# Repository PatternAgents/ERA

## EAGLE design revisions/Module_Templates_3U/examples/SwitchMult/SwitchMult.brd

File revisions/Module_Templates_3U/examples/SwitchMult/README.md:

# SwitchMult

Format : ERA / Eurorack

Height : 3U 

Width: 4HP

Depth : 1.0 cm

Power : +12V 35mA

Jacks : 3.5mm Jacks (Thonkiconn PJ301M-12)

A simple, passive, "Switched Multiple" design for ERA/Eurorack. 
Four(4) latching, LED illuminated, pushbutton switches, 
control up to four (4) input/outputs,
that are routed to an internal bus.
The four inputs (P1-P4) are "normalized" to the ERA bus signals as follows:

1) ERA Bus Gate In  (Green)
2) ERA Bus CV In    (Red)
3) ERA Bus Gate Out (Blue)
4) ERA Bus CV Out   (Yellow)

When connected to an ERA backplane, those Bus signals can be routed to other
"Switched Multiple" modules, or other ERA audio/video modules.

-----------------------------------------------------
This repository contains Open Source Hardware Reference Designs for Embedded Rack Architecture (ERA)
that anyone can use or fabricate for themselves.

For more information, please see the [ERA Wiki](https://github.com/halcyonmodular/ERA/wiki)!

Embedded Rack Architecture (ERA) is a new, Open Source Hardware (OSHW) specification for 
Modular Audio/Video equipment that is being co-developed by a number of
cooperating companies and individuals in the audio field,
and is completely backward compatible with Eurorack (Legacy). 

-----------------------------------------------------

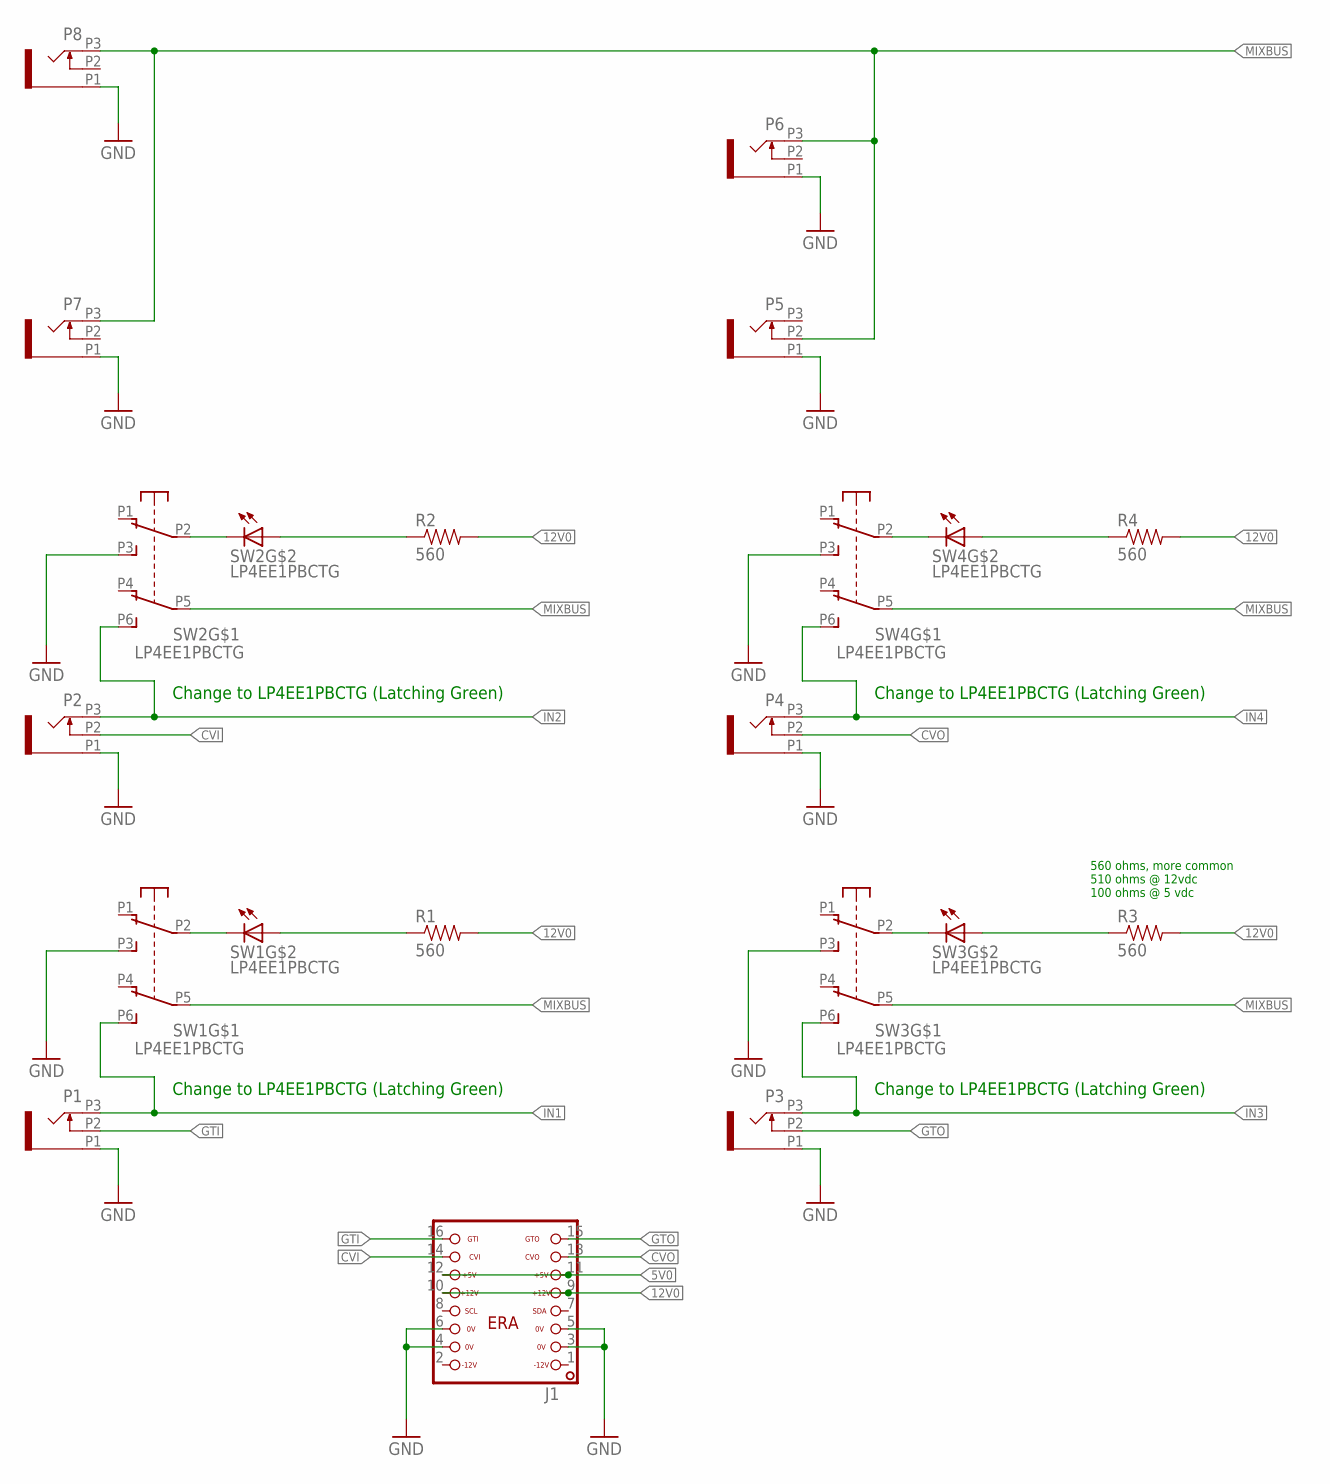
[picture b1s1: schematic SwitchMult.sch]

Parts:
J1: ERA-SHROUD; ERA
P1, P2, P3, P4, P5, P6, P7, P8: PJ301_THONKICONN6; WQP_PJ_301M6
R1, R2, R3, R4: 560; AXIAL-0.4
SW1, SW2, SW3, SW4: LP4EE1PBCTG; LP4OA1PBCT

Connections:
5V0: J1.11, J1.12
12V0: J1.9, J1.10, R1.P$2 (2), R2.P$2 (2), R3.P$2 (2), R4.P$2 (2)
CVI: J1.14, P2.P2 (2)
CVO: J1.13, P4.P2 (2)
GND: J1.3, J1.4, J1.5, J1.6, P1.P1 (1), P2.P1 (1), P3.P1 (1), P4.P1 (1), P5.P1 (1), P6.P1 (1), P7.P1 (1), P8.P1 (1), SW1.P3 (A3), SW2.P3 (A3), SW3.P3 (A3), SW4.P3 (A3)
GTI: J1.16, P1.P2 (2)
GTO: J1.15, P3.P2 (2)
IN1: P1.P3 (3), SW1.P6 (B3)
IN2: P2.P3 (3), SW2.P6 (B3)
IN3: P3.P3 (3), SW3.P6 (B3)
IN4: P4.P3 (3), SW4.P6 (B3)
MIXBUS: P5.P2 (2), P6.P3 (3), P7.P3 (3), P8.P3 (3), SW1.P5 (B2), SW2.P5 (B2), SW3.P5 (B2), SW4.P5 (B2)
unnamed: SW1.L2, SW1.P2 (A2)
unnamed: SW2.L2, SW2.P2 (A2)
unnamed: R1.P$1 (1), SW1.L1
unnamed: R2.P$1 (1), SW2.L1
unnamed: SW3.L2, SW3.P2 (A2)
unnamed: R3.P$1 (1), SW3.L1
unnamed: SW4.L2, SW4.P2 (A2)
unnamed: R4.P$1 (1), SW4.L1

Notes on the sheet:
Change to LP4EE1PBCTG (Latching Green)
560 ohms, more common 510 ohms @ 12vdc 100 ohms @ 5 vdc

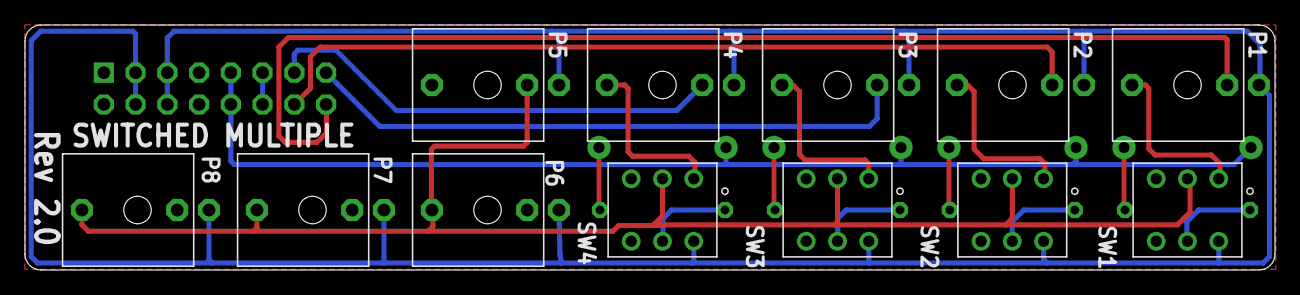
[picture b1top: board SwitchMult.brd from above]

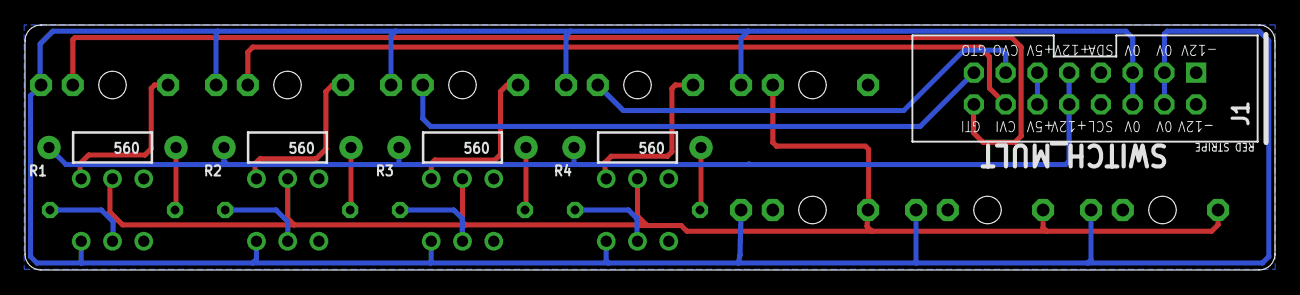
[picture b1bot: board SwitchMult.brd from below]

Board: 2 copper layers, 100.0 x 19.6 mm, 17 parts (5 on the bottom side), 20 nets.

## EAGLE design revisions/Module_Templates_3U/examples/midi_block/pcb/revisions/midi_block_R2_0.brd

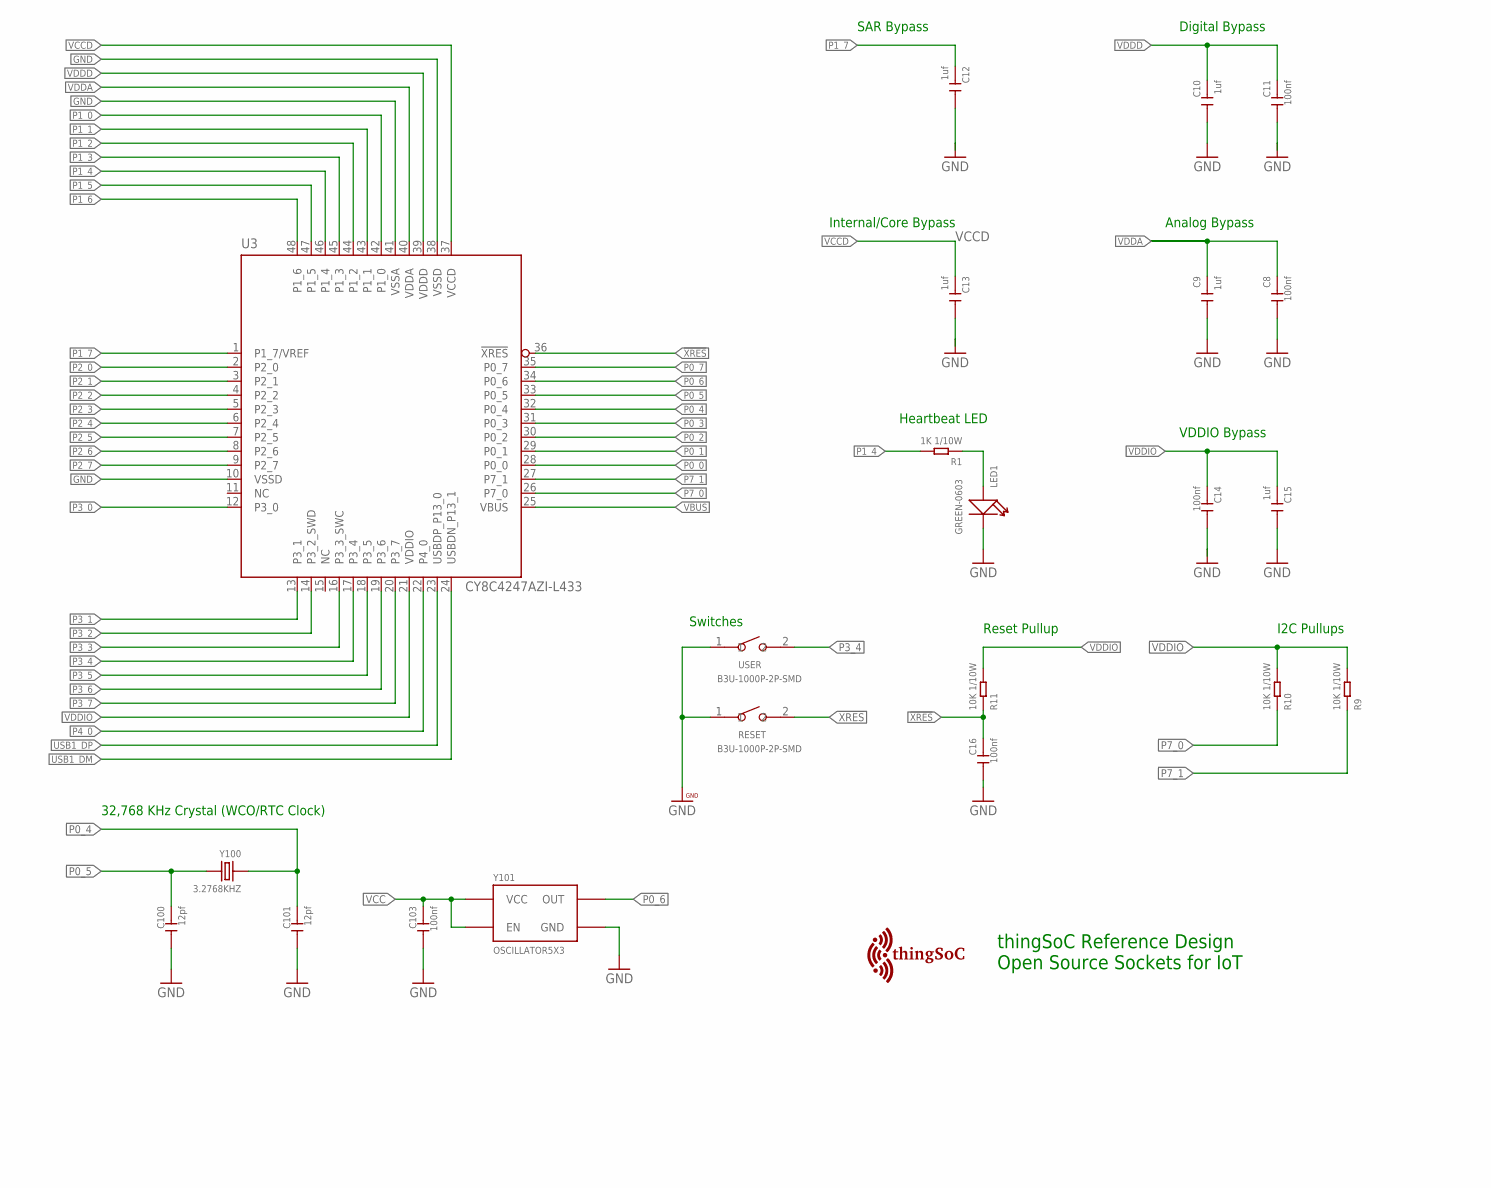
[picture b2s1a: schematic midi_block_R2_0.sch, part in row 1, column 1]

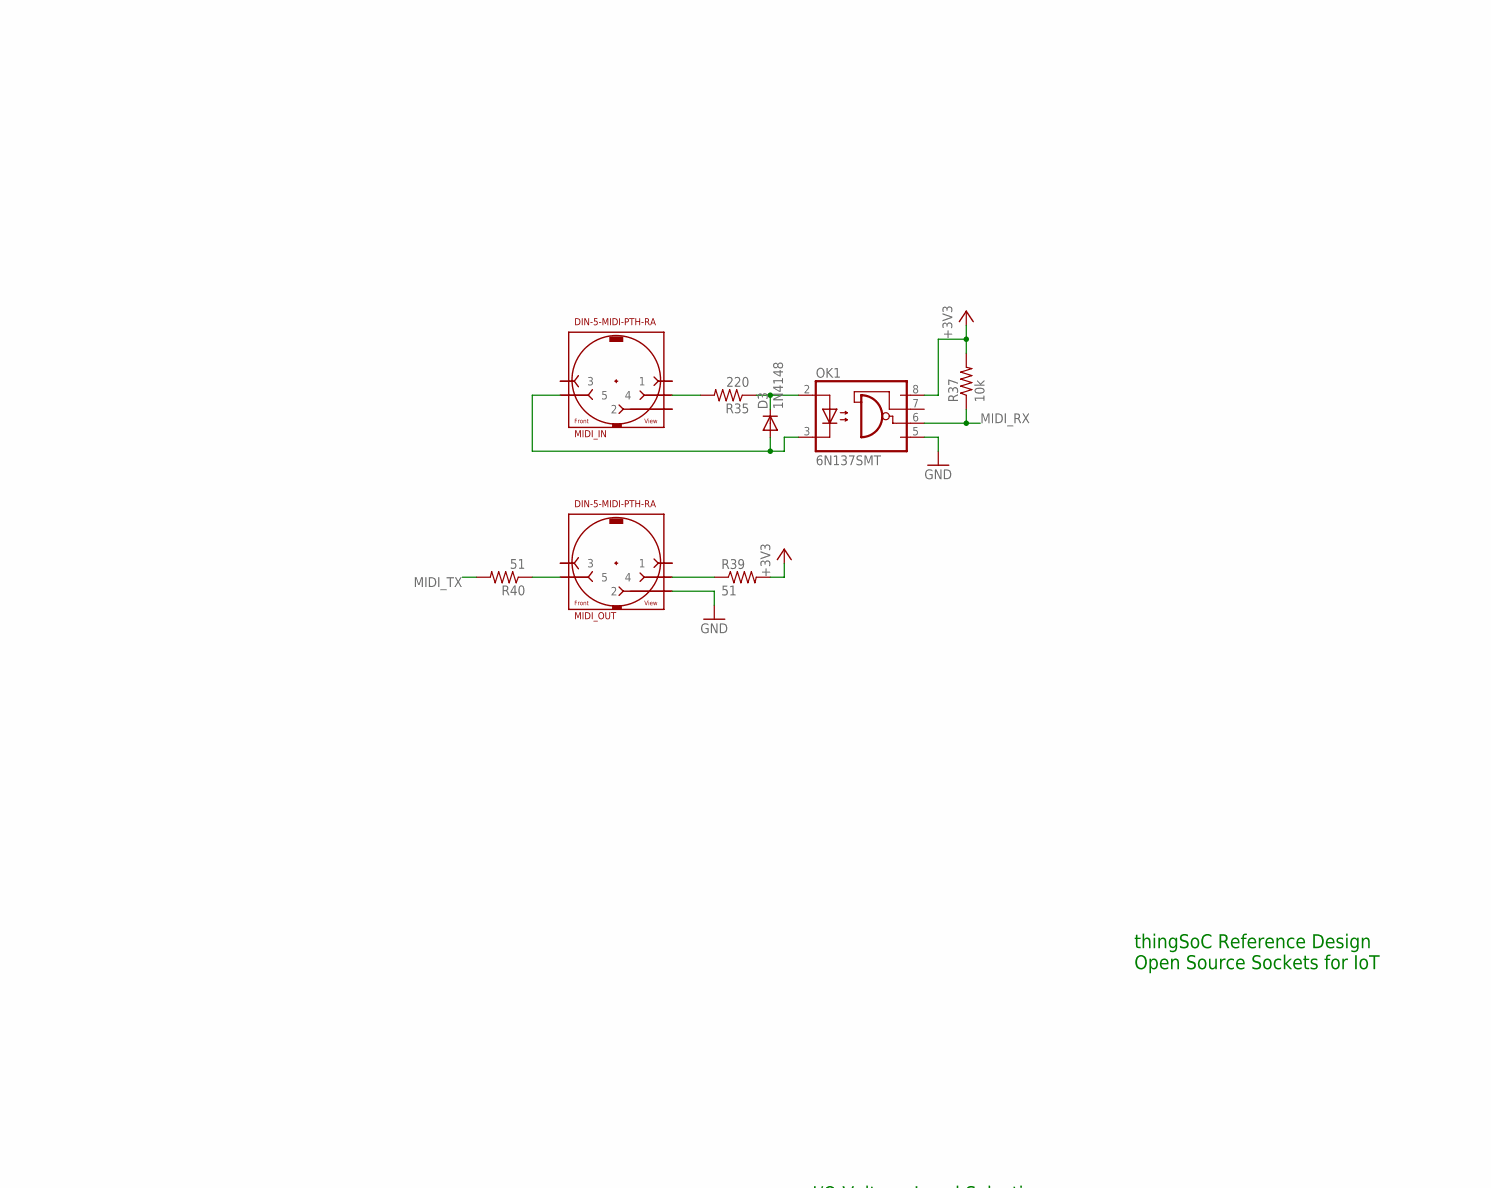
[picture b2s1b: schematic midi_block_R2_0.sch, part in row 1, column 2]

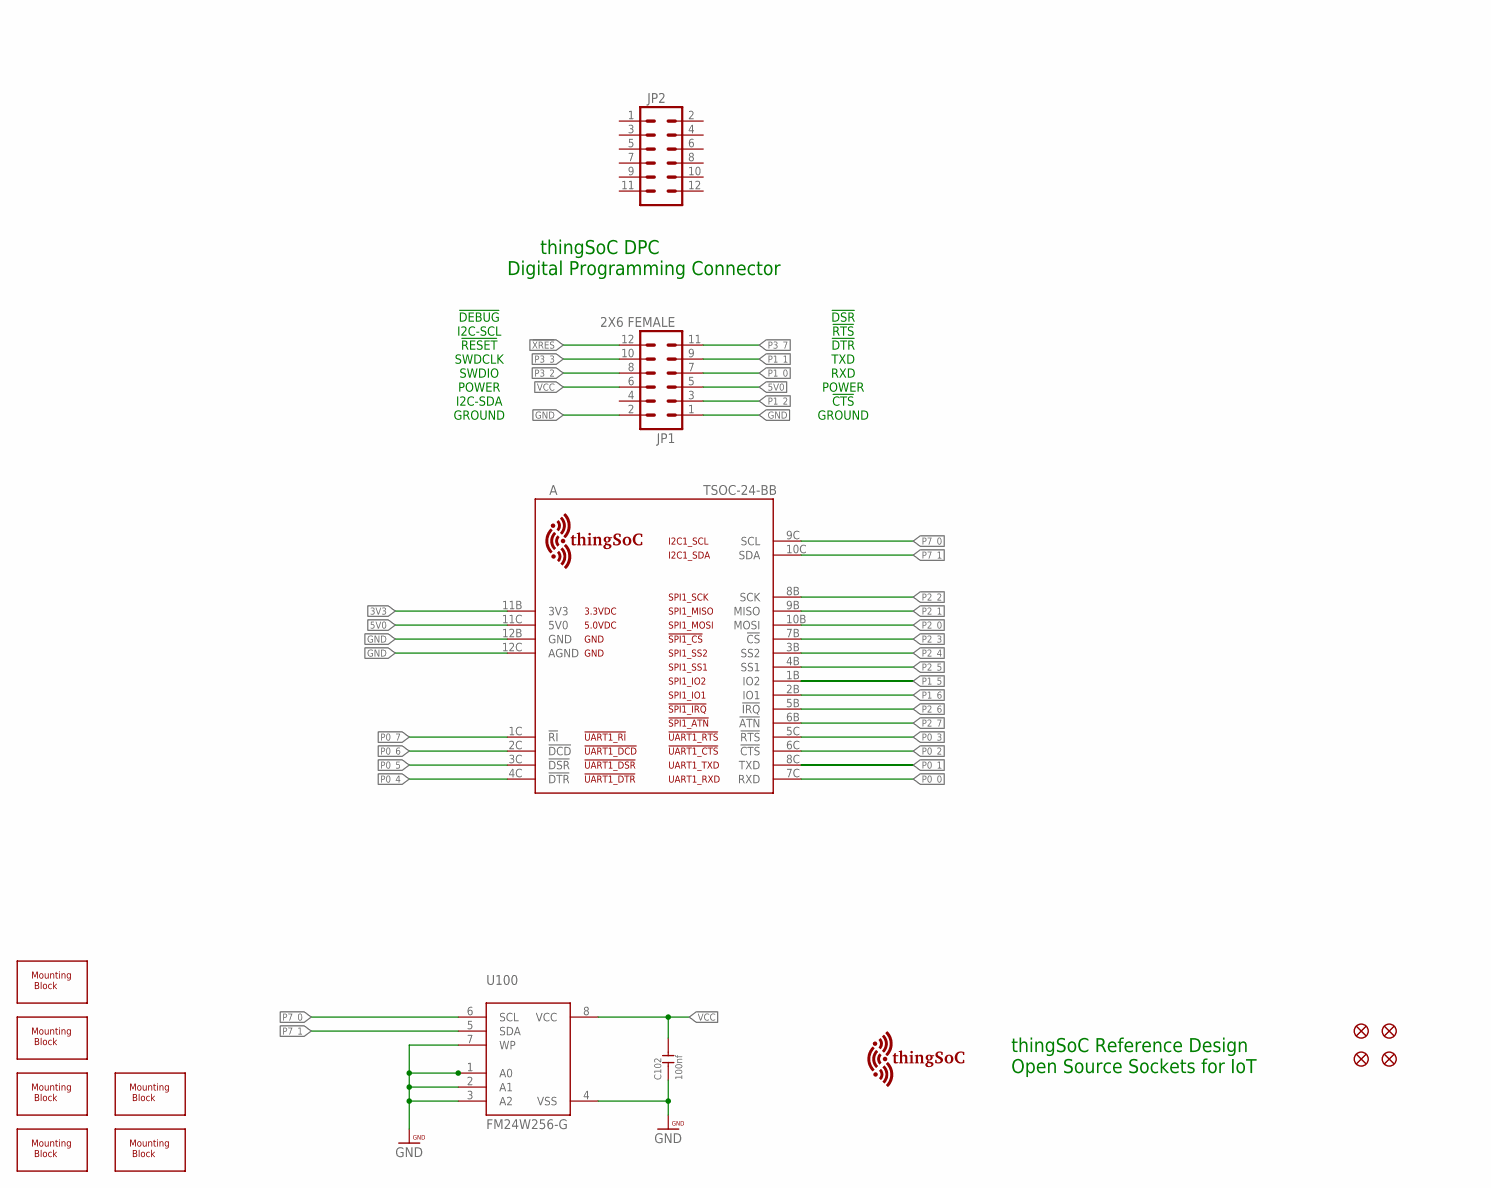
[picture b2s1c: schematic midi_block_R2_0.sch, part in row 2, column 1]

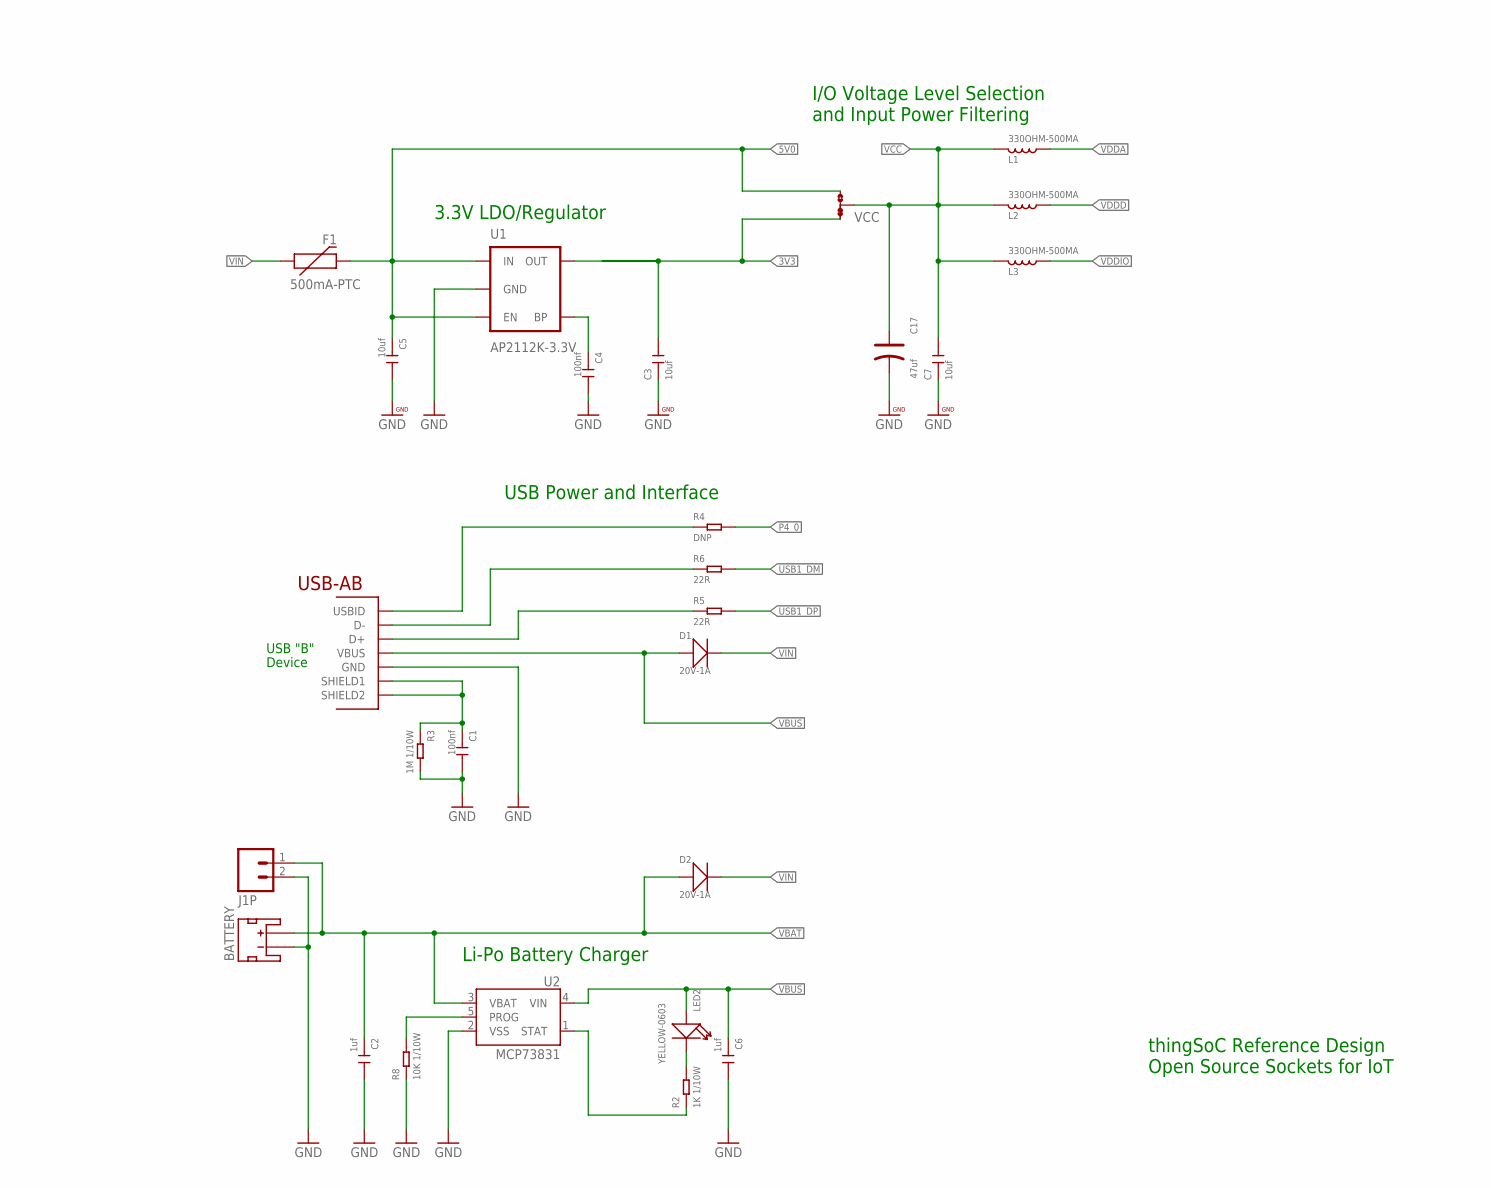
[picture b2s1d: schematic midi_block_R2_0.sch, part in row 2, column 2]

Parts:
A: TSOC-24-BB; TSOC-BB-S24
BATTERY: JST_2MM_MALE; JST-2-SMD
C1, C4, C8, C11, C14, C16, C102, C103: 100nf; C0603
C2, C6, C9, C10, C12, C13, C15: 1uf; C0603
C3, C5, C7: 10uf; C0603
C17: 47uf; AVX-A
C100, C101: 12pf; C0603
D1, D2: 20V-1A; SOD-123
D3: 1N4148; SOD323-W
F1: 500mA-PTC; PTC-1206
FID1, FID2, FID3, FID4: FIDUCIALUFIDUCIAL; MICRO-FIDUCIAL
J1P: M02-JST-2-PTH-NO_SILK; JST-2-PTH-NS
JP1: 2X6 FEMALE; 2X6
JP2: M06X2FEMALE-SMT; 2X6_SMD
L1, L2, L3: 330OHM-500MA; L0603
LED1: GREEN-0603; LED-0603
LED2: YELLOW-0603; LED-0603
MIDI_IN: DIN-5-MIDI-PTH-RA; DIN-5-PTH-RA-SUPPORT
MIDI_OUT: DIN-5-MIDI-PTH-RA; DIN-5-PTH-RA-SUPPORT
OK1: 6N137SMT; DIL8-SMD
R1, R2: 1K 1/10W; R0603
R3: 1M 1/10W; R0603
R4: DNP; R0603
R5, R6: 22R; R0603
R8, R9, R10, R11: 10K 1/10W; R0603
R35: 220; R0603
R37: 10k; R0603
R39, R40: 51; R0603
RESET: B3U-1000P-2P-SMD; SW2-2.6-3.0X2.5X1.2+0.4MM
U1: AP2112K-3.3V; SOT23-5
U2: MCP73831; SOT23-5
U3: CY8C4247AZI-L433; TQFP-7X7-48
U100: FM24W256-G; SO08
U$1, U$7, U$8, U$9, U$10, U$11: PCB-MB-SIDE; PCB-MB-01-SIDE
U$100: TSOC-LOGO-LRG
U$101: TSOC-LOGO-SMALL; TSOC-LOGO-SML
USB: USB_AB; USB-AB-MICRO-SMD
USER: B3U-1000P-2P-SMD; SW2-2.6-3.0X2.5X1.2+0.4MM
VCC: JMP-3-1_2
Y100: 3.2768KHZ; X2-SMD-L2.0X1.2X0.55MM
Y101: OSCILLATOR5X3; CRYSTAL-SMD-5X3

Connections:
3V3: A.11B (3V3), C3.2, U1.5 (OUT), VCC.1
5V0: A.11C (5V0), C5.1, F1.2, JP1.5, U1.1 (IN), U1.3 (EN), VCC.3
!XRES: C16.1, JP1.12, R11.1, RESET.2, U3.36 (!XRES)
+3V3: OK1.8 (VCC), R37.2, R39.2
BYPASS1: C4.1, U1.4 (BP)
CLED: LED2.-, R2.2
CSTAT: R2.1, U2.1 (STAT)
GND: A.12B (GND), A.12C (AGND), BATTERY.1 (-), C1.2, C2.2, C3.1, C4.2, C5.2, C6.2, C7.1, C8.2, C9.2, C10.2, C11.2, C12.2, C13.2, C14.2, C15.2, C16.2, C17.-, C100.2, C101.2, C102.1, C103.2, J1P.2, JP1.1, JP1.2, LED1.-, MIDI_OUT.2, OK1.5 (GND), R3.2, R8.1, RESET.1, U1.2 (GND), U2.2 (VSS), U3.10 (VSSD), U3.38 (VSSD), U3.41 (VSSA), U100.1 (A0), U100.2 (A1), U100.3 (A2), U100.4 (VSS), U100.7 (WP), USB.GND, USER.1, Y101.2 (GND)
MIDI_RX: OK1.6 (VO), R37.1
MIDI_TX: R40.2
unnamed: R8.2, U2.5 (PROG)
unnamed: D3.C, OK1.2 (A), R35.1
unnamed: MIDI_IN.4, R35.2
unnamed: MIDI_OUT.5, R40.1
unnamed: D3.A, MIDI_IN.5, OK1.3 (C)
unnamed: MIDI_OUT.4, R39.1
unnamed: LED1.+, R1.1
P0_0: A.7C (RXD), U3.28 (P0_0)
P0_1: A.8C (TXD), U3.29 (P0_1)
P0_2: A.6C (!CTS), U3.30 (P0_2)
P0_3: A.5C (!RTS), U3.31 (P0_3)
P0_4: A.4C (!DTR), C101.1, U3.32 (P0_4), Y100.1
P0_5: A.3C (!DSR), C100.1, U3.33 (P0_5), Y100.2
P0_6: A.2C (!DCD), U3.34 (P0_6), Y101.3 (OUT)
P0_7: A.1C (!RI), U3.35 (P0_7)
P1_0: JP1.7, U3.42 (P1_0)
P1_1: JP1.9, U3.43 (P1_1)
P1_2: JP1.3, U3.44 (P1_2)
P1_3: U3.45 (P1_3)
P1_4: R1.2, U3.46 (P1_4)
P1_5: A.1B (IO2), U3.47 (P1_5)
P1_6: A.2B (IO1), U3.48 (P1_6)
P1_7: C12.1, U3.1 (P1_7/VREF)
P2_0: A.10B (MOSI), U3.2 (P2_0)
P2_1: A.9B (MISO), U3.3 (P2_1)
P2_2: A.8B (SCK), U3.4 (P2_2)
P2_3: A.7B (!CS), U3.5 (P2_3)
P2_4: A.3B (SS2), U3.6 (P2_4)
P2_5: A.4B (SS1), U3.7 (P2_5)
P2_6: A.5B (!IRQ), U3.8 (P2_6)
P2_7: A.6B (!ATN), U3.9 (P2_7)
P3_0: U3.12 (P3_0)
P3_1: U3.13 (P3_1)
P3_2: JP1.8, U3.14 (P3_2_SWD)
P3_3: JP1.10, U3.16 (P3_3_SWC)
P3_4: U3.17 (P3_4), USER.2
P3_5: U3.18 (P3_5)
P3_6: U3.19 (P3_6)
P3_7: JP1.11, U3.20 (P3_7)
P4_0: R4.2, U3.22 (P4_0)
P7_0: A.9C (SCL), R10.1, U3.26 (P7_0), U100.6 (SCL)
P7_1: A.10C (SDA), R9.1, U3.27 (P7_1), U100.5 (SDA)
USB1_DM: R6.2, U3.24 (USBDN_P13_1)
USB1_DP: R5.2, U3.23 (USBDP_P13_0)
USB1_I: R4.1, USB.ID (USBID)
USB1_M: R6.1, USB.D-
USB1_P: R5.1, USB.D+
USB1_SHIELD: C1.1, R3.1, USB.SHIELD1, USB.SHIELD2
VBAT: BATTERY.2 (+), C2.1, D2.+, J1P.1, U2.3 (VBAT)
VBUS: C6.1, D1.+, LED2.+, U2.4 (VIN), U3.25 (VBUS), USB.VBUS
VCC: C7.2, C17.+, C102.2, C103.1, JP1.6, L1.1, L2.1, L3.1, U100.8 (VCC), VCC.2, Y101.1 (EN), Y101.4 (VCC)
VCCD: C13.1, U3.37 (VCCD)
VDDA: C8.1, C9.1, L1.2, U3.40 (VDDA)
VDDD: C10.1, C11.1, L2.2, U3.39 (VDDD)
VDDIO: C14.1, C15.1, L3.2, R9.2, R10.2, R11.2, U3.21 (VDDIO)
VIN: D1.-, D2.-, F1.1

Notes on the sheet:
Internal/Core Bypass
Digital Bypass
VDDIO Bypass
SAR Bypass
USB "B"
Device
3.3V LDO/Regulator
Reset Pullup
Heartbeat LED
Analog Bypass
Li-Po Battery Charger
USB Power and Interface
I/O Voltage Level Selection and Input Power Filtering
I2C Pullups
thingSoC Reference Design Open Source Sockets for IoT
I2C-SDA
I2C-SCL
!RESET
SWDCLK
SWDIO
POWER
GROUND
!DEBUG
!DSR
!RTS
!CTS
!DTR
TXD
RXD
thingSoC DPC Digital Programming Connector
Switches
32,768 KHz Crystal (WCO/RTC Clock)

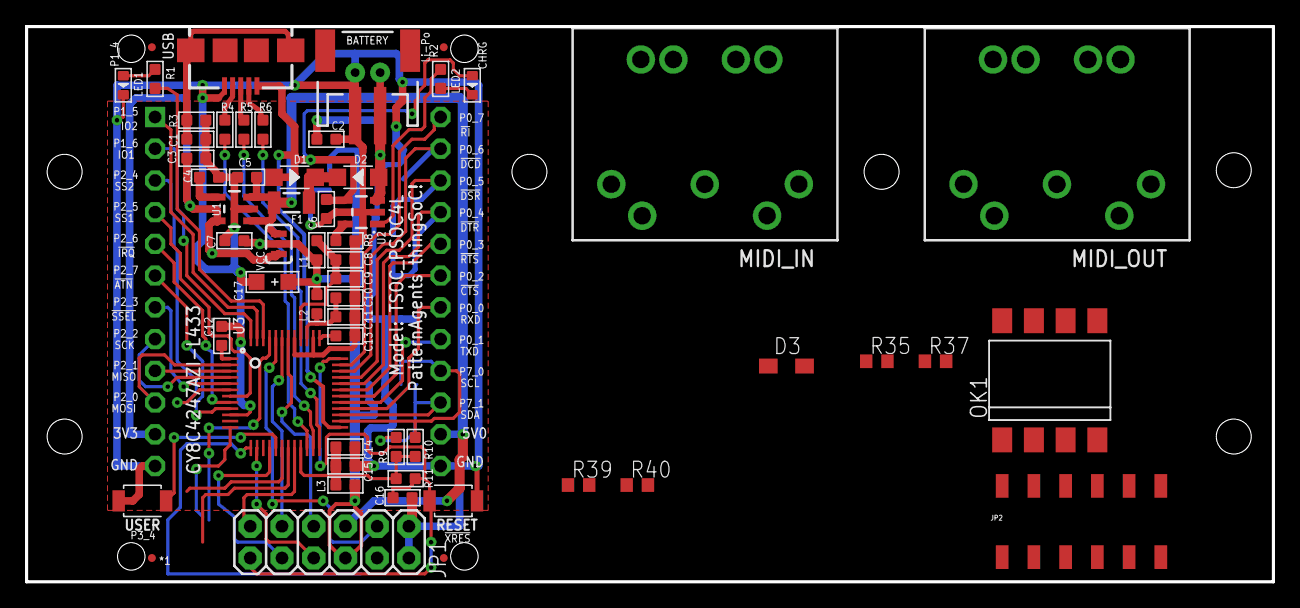
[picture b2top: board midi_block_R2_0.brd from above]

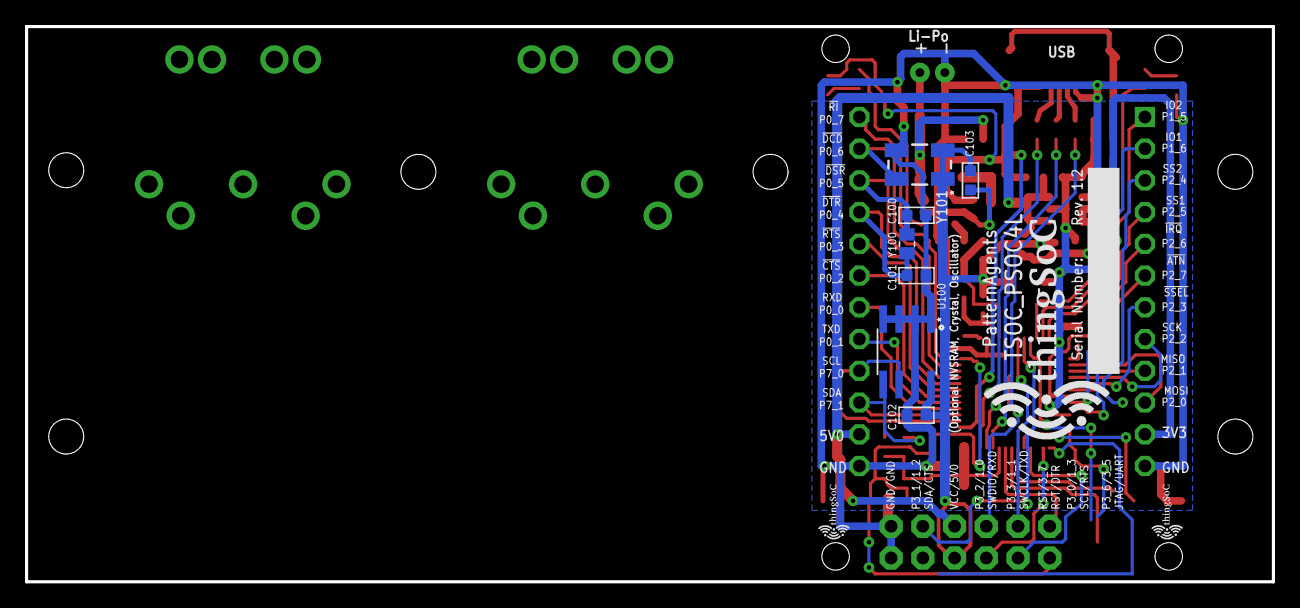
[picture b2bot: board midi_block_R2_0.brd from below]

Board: 2 copper layers, 99.8 x 44.5 mm, 75 parts (11 on the bottom side), 60 nets.

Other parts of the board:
U$102: TSOC-LOGO-SMALL; TSOC-LOGO-SML

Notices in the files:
revisions/Module_Templates_3U/examples/SwitchMult/README.md:
License: CC BY 4.0
parts and their libraries:
PatternAgents-Beautify: License : http://creativecommons.org/licenses/by-sa/3.0
(Creative Commons 3.0)
thingSoC: License : http://creativecommons.org/licenses/by-sa/4.0
(Creative Commons 4.0)
